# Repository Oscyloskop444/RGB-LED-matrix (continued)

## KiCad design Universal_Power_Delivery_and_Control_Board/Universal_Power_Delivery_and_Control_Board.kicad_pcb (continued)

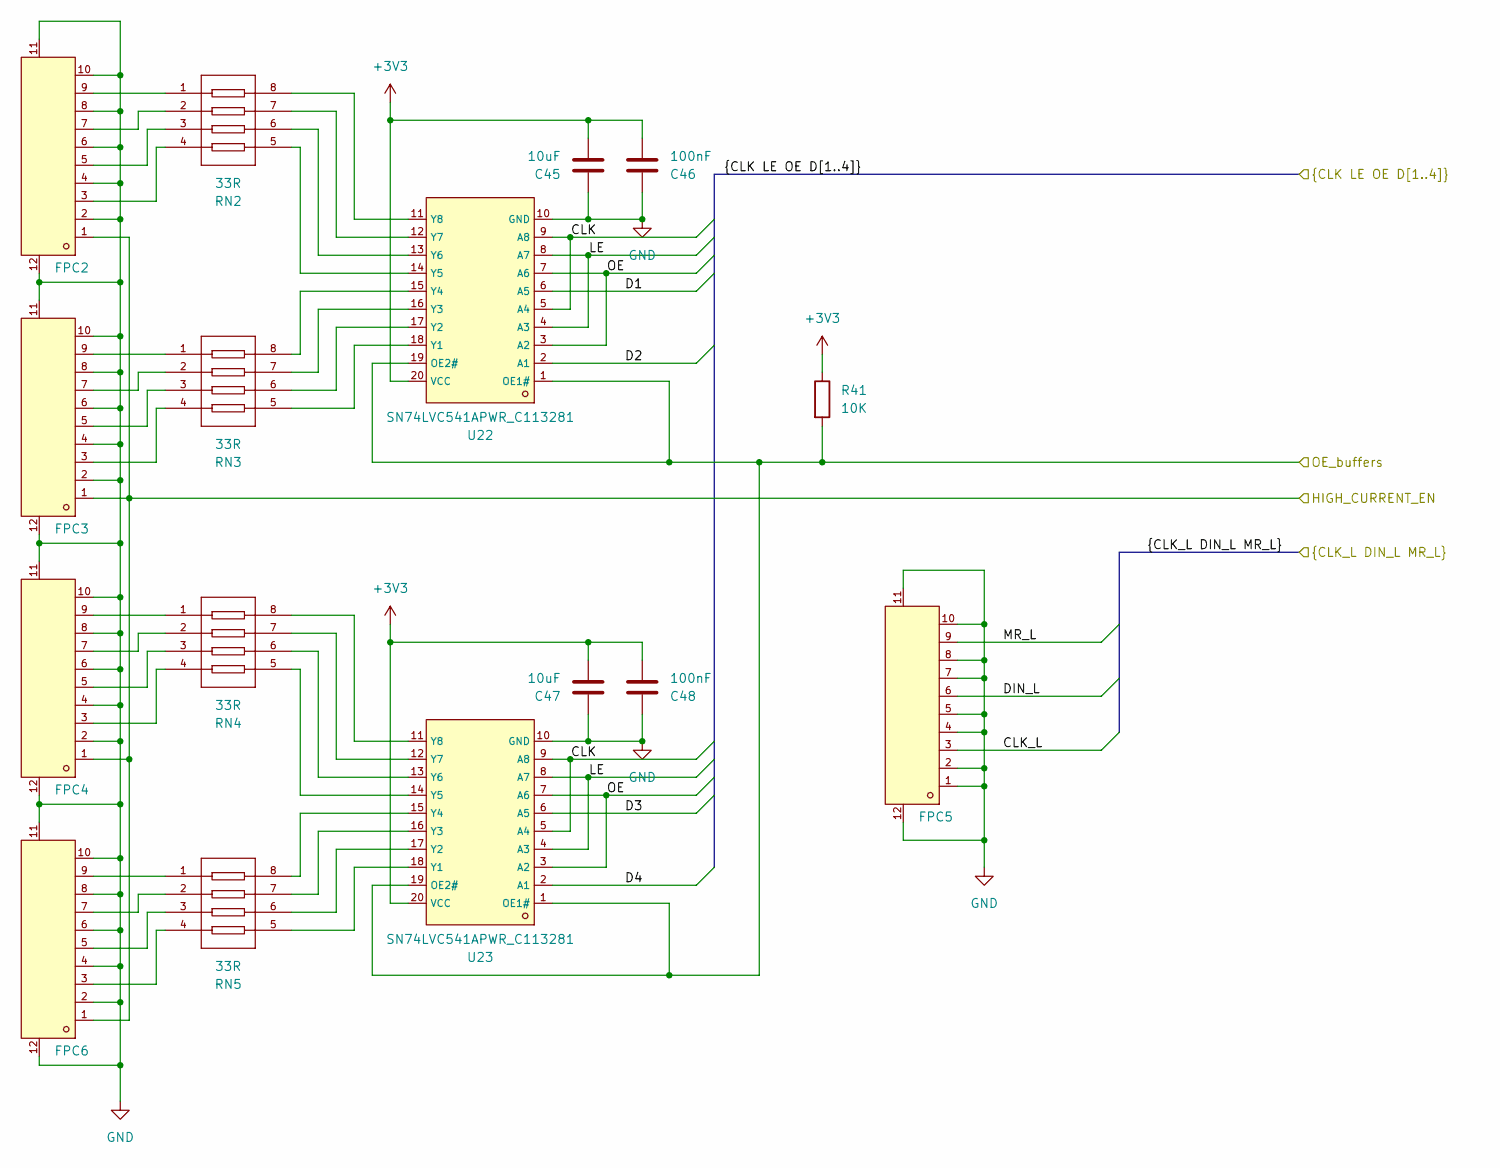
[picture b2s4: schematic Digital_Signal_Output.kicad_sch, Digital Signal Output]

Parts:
C45, C47: 10uF; C_0805_2012Metric_Pad1.18x1.45mm_HandSolder
C46, C48: 100nF; C_0402_1005Metric_Pad0.74x0.62mm_HandSolder
FPC2, FPC3, FPC4, FPC5, FPC6: XW05202-100R-00; C2906114_FPC-SMD_10P-P0_50_HCTL_XW05202-100R-00; LCSC C2906114
R41: 10K; R_0402_1005Metric_Pad0.72x0.64mm_HandSolder
RN2, RN3, RN4, RN5: 33R; C165956_RES-ARRAY-SMD_0603-8P-L3_2-W1_6-BL; LCSC C165956
U22, U23: SN74LVC541APWR_C113281; C113281_TSSOP-20_L6_5-W4_4-P0_65-LS6_4-BL; LCSC C113281

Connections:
+3V3: C45.2, C46.2, C47.2, C48.2, R41.1, U22.20 (VCC), U23.20 (VCC); also elsewhere on the board
/Digital_Signal_Output/CLK_L: FPC5.3; also elsewhere on the board
/Digital_Signal_Output/D1: U22.6 (A5); also elsewhere on the board
/Digital_Signal_Output/D2: U22.2 (A1); also elsewhere on the board
/Digital_Signal_Output/D3: U23.6 (A5); also elsewhere on the board
/Digital_Signal_Output/D4: U23.2 (A1); also elsewhere on the board
/Digital_Signal_Output/DIN_L: FPC5.6; also elsewhere on the board
/Digital_Signal_Output/HIGH_CURRENT_EN: FPC2.1, FPC3.1, FPC4.1, FPC6.1; also elsewhere on the board
/Digital_Signal_Output/MR_L: FPC5.9; also elsewhere on the board
/Digital_Signal_Output/OE_buffers: R41.2, U22.1 (OE1#), U22.19 (OE2#), U23.1 (OE1#), U23.19 (OE2#); also elsewhere on the board
/Power_Output/5V_O1: U22.5 (A4), U22.9 (A8), U23.5 (A4), U23.9 (A8); also elsewhere on the board
/Power_Output/5V_O2: U22.4 (A3), U22.8 (A7), U23.4 (A3), U23.8 (A7); also elsewhere on the board
/Power_Output/5V_O3: U22.3 (A2), U22.7 (A6), U23.3 (A2), U23.7 (A6); also elsewhere on the board
GND: C45.1, C46.1, C47.1, C48.1, FPC2.2, FPC2.4, FPC2.6, FPC2.8, FPC2.10, FPC2.11, FPC2.12, FPC3.2, FPC3.4, FPC3.6, FPC3.8, FPC3.10, FPC3.11, FPC3.12, FPC4.2, FPC4.4, FPC4.6, FPC4.8, FPC4.10, FPC4.11, FPC4.12, FPC5.1, FPC5.2, FPC5.4, FPC5.5, FPC5.7, FPC5.8, FPC5.10, FPC5.11, FPC5.12, FPC6.2, FPC6.4, FPC6.6, FPC6.8, FPC6.10, FPC6.11, FPC6.12, U22.10 (GND), U23.10 (GND); also elsewhere on the board
unnamed: FPC2.3, RN2.4
unnamed: FPC2.5, RN2.3
unnamed: FPC2.7, RN2.2
unnamed: FPC2.9, RN2.1
unnamed: FPC3.3, RN3.4
unnamed: FPC3.5, RN3.3
unnamed: FPC3.7, RN3.2
unnamed: FPC3.9, RN3.1
unnamed: FPC4.3, RN4.4
unnamed: FPC4.5, RN4.3
unnamed: FPC4.7, RN4.2
unnamed: FPC4.9, RN4.1
unnamed: FPC6.3, RN5.4
unnamed: FPC6.5, RN5.3
unnamed: FPC6.7, RN5.2
unnamed: FPC6.9, RN5.1
unnamed: RN3.5, U22.18 (Y1)
unnamed: RN3.6, U22.17 (Y2)
unnamed: RN3.7, U22.16 (Y3)
unnamed: RN3.8, U22.15 (Y4)
unnamed: RN2.5, U22.14 (Y5)
unnamed: RN2.6, U22.13 (Y6)
unnamed: RN2.7, U22.12 (Y7)
unnamed: RN2.8, U22.11 (Y8)
unnamed: RN5.5, U23.18 (Y1)
unnamed: RN5.6, U23.17 (Y2)
unnamed: RN5.7, U23.16 (Y3)
unnamed: RN5.8, U23.15 (Y4)
unnamed: RN4.5, U23.14 (Y5)
unnamed: RN4.6, U23.13 (Y6)
unnamed: RN4.7, U23.12 (Y7)
unnamed: RN4.8, U23.11 (Y8)

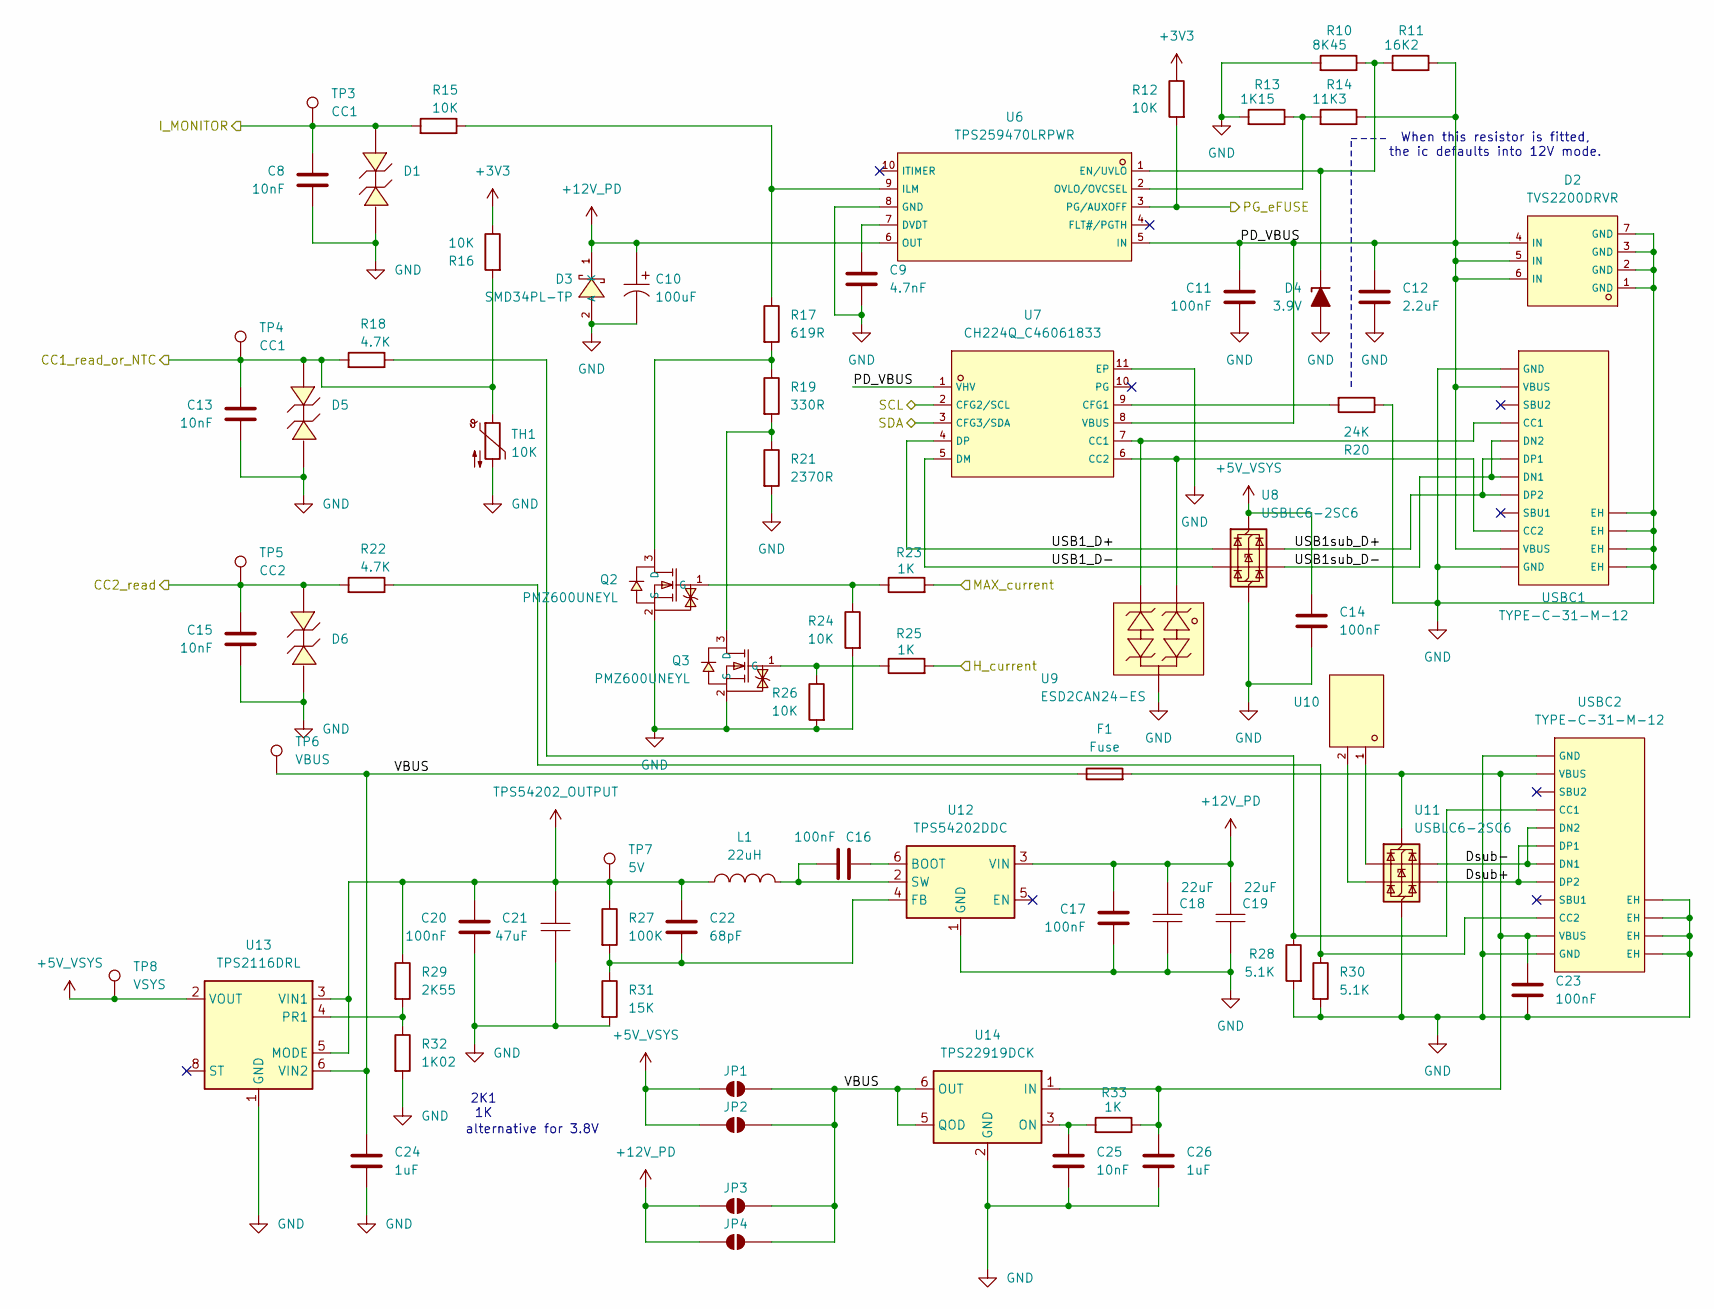
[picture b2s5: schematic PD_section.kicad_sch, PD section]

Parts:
C8, C13, C15, C25: 10nF; C_0402_1005Metric_Pad0.74x0.62mm_HandSolder
C9: 4.7nF; C_0402_1005Metric
C10: 100uF; C19673858_CAP-SMD_BD6_3-L6_5-W6_5-LS7_2-FD_1; LCSC C19673858
C11, C14, C16, C17, C20, C23: 100nF; C_0402_1005Metric_Pad0.74x0.62mm_HandSolder
C12: 2.2uF; C_0805_2012Metric
C18, C19: 22uF; C778721_C1210; LCSC C778721
C21: 47uF; C426659_C1206; LCSC C426659
C22: 68pF; C_0402_1005Metric_Pad0.74x0.62mm_HandSolder
C24: 1uF; C_0402_1005Metric_Pad0.74x0.62mm_HandSolder
C26: 1uF; C_0603_1608Metric_Pad1.08x0.95mm_HandSolder
D1, D5, D6: PESDNC2FD3V3BS; C496536_DFN1006-2L-BI; LCSC C496536
D2: TVS2200DRVR; C523793_WSON-6_L2_0-W2_0-P0_65-BL-EP; LCSC C523793
D3: SMD34PL-TP; C725481_SOD-123FL_L2_8-W1_7-LS3_6-RD; LCSC C725481
D4: 3.9V; D_SOD-882
F1: Fuse; Fuse_1206_3216Metric_Pad1.42x1.75mm_HandSolder
JP1, JP2, JP3, JP4: SolderJumper_2_Open; SolderJumper-2_P1.3mm_Open_RoundedPad1.0x1.5mm
L1: 22uH; C138686_IND-SMD_L10_7-W10_0; LCSC C138686
Q2, Q3: PMZ600UNEYL; C547286_SOT-883-3_L1_0-W0_6-BR; LCSC C547286
R10: 8K45; R_0402_1005Metric_Pad0.72x0.64mm_HandSolder
R11: 16K2; R_0402_1005Metric_Pad0.72x0.64mm_HandSolder
R12, R15, R16: 10K; R_0402_1005Metric_Pad0.72x0.64mm_HandSolder
R13: 1K15; R_0402_1005Metric_Pad0.72x0.64mm_HandSolder
R14: 11K3; R_0402_1005Metric_Pad0.72x0.64mm_HandSolder
R17: 619R; R_0402_1005Metric
R18, R22: 4.7K; R_0402_1005Metric_Pad0.72x0.64mm_HandSolder
R19: 330R; R_0402_1005Metric
R20: 24K; R_0402_1005Metric_Pad0.72x0.64mm_HandSolder
R21: 2370R; R_0402_1005Metric
R23, R25, R33: 1K; R_0402_1005Metric_Pad0.72x0.64mm_HandSolder
R24, R26: 10K; R_0402_1005Metric
R27: 100K; R_0402_1005Metric_Pad0.72x0.64mm_HandSolder
R28, R30: 5.1K; R_0402_1005Metric_Pad0.72x0.64mm_HandSolder
R29: 2K55; R_0402_1005Metric_Pad0.72x0.64mm_HandSolder
R31: 15K; R_0402_1005Metric_Pad0.72x0.64mm_HandSolder
R32: 1K02; R_0402_1005Metric_Pad0.72x0.64mm_HandSolder
TH1: 10K; R_0402_1005Metric_Pad0.72x0.64mm_HandSolder
TP3, TP4: CC1; TestPoint_Pad_D1.0mm
TP5: CC2; TestPoint_Pad_D1.0mm
TP6: VBUS; TestPoint_Pad_D1.0mm
TP7: 5V; TestPoint_Pad_D1.0mm
TP8: VSYS; TestPoint_Pad_D1.0mm
U6: TPS259470LRPWR; C3662793_VQFN-10_L2_0-W2_0-P0_45-TL; LCSC C3662793
U7: CH224Q_C46061833; C46061833_DFN-10_L2_0-W2_0-P0_40-BL-EP; LCSC C46061833
U8, U11: USBLC6-2SC6; SOT-23-6
U9: ESD2CAN24-ES; C19170841_SOT-23-3_L2_9-W1_3-P1_90-LS2_4-BR; LCSC C19170841
U10: S2B-ZR (LF)(SN); C157930_CONN-TH_S2B-ZR-LF-SN; LCSC C157930
U12: TPS54202DDC; SOT-23-6
U13: TPS2116DRL; SOT-583-8
U14: TPS22919DCK; SOT-363_SC-70-6
USBC1, USBC2: TYPE-C-31-M-12; C165948_USB-C_SMD-TYPE-C-31-M-12_1; LCSC C165948

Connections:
+3V3: R12.1, R16.1; also elsewhere on the board
+5V_VSYS: C14.1, JP1.1 (A), JP2.1 (A), TP8.1 (1_1), U8.5 (VBUS), U13.2 (VOUT), U13.7 (VOUT); also elsewhere on the board
+12V_PD: C10.1, C17.1, C18.2, C19.2, D3.1 (K), JP3.1 (A), JP4.1 (A), U6.6 (OUT), U12.3 (VIN); also elsewhere on the board
/P00: R12.2, U6.3 (PG/AUXOFF); also elsewhere on the board
/PD_Section/CC1_read_or_NTC: C13.1, D5.2, R16.2, R18.2, TH1.1, TP4.1 (1_1); also elsewhere on the board
/PD_Section/CC2_read: C15.1, D6.2, R22.2, TP5.1 (1_1); also elsewhere on the board
/PD_Section/Dsub+: U11.4 (I/O2), USBC2.A6 (DP1), USBC2.B6 (DP2)
/PD_Section/Dsub-: U11.6 (I/O1), USBC2.A7 (DN1), USBC2.B7 (DN2)
/PD_Section/H_current: R25.2; also elsewhere on the board
/PD_Section/I_MONITOR: C8.1, D1.2, R15.2, TP3.1 (1_1); also elsewhere on the board
/PD_Section/MAX_current: R23.2; also elsewhere on the board
/PD_Section/PD_VBUS: C11.1, C12.1, D2.4 (IN), D2.5 (IN), D2.6 (IN), R11.1, R14.1, U6.5 (IN), U7.1 (VHV), U7.8 (VBUS), USBC1.A4B9 (VBUS), USBC1.B4A9 (VBUS)
/PD_Section/USB1_D+: U7.4 (DP), U8.1 (I/O1)
/PD_Section/USB1_D-: U7.5 (DM), U8.3 (I/O2)
/PD_Section/USB1sub_D+: U8.6 (I/O1), USBC1.A6 (DP1), USBC1.B6 (DP2)
/PD_Section/USB1sub_D-: U8.4 (I/O2), USBC1.A7 (DN1), USBC1.B7 (DN2)
/PD_Section/VBUS: C24.1, F1.1, JP1.2 (B), JP2.2 (B), JP3.2 (B), JP4.2 (B), TP6.1 (1_1), U13.6 (VIN2), U14.5 (QOD), U14.6 (OUT)
/SCL: U7.2 (CFG2/SCL); also elsewhere on the board
/SDA: U7.3 (CFG3/SDA); also elsewhere on the board
GND: C8.2, C9.2, C10.2, C11.2, C12.2, C13.2, C14.2, C15.2, C17.2, C18.1, C19.1, C20.2, C21.1, C23.2, C24.2, C25.2, C26.2, D1.1, D2.1 (GND), D2.2 (GND), D2.3 (GND), D2.7 (GND), D3.2 (A), D4.2 (A), D5.1, D6.1, Q2.2 (S), Q3.2 (S), R10.2, R13.2, R20.1, R21.2, R24.2, R26.2, R28.2, R30.2, R31.2, R32.2, TH1.2, U6.8 (GND), U7.11 (EP), U8.2 (GND), U9.3 (GND), U11.2 (GND), U12.1 (GND), U13.1 (GND), U14.2 (GND), USBC1.1 (EH), USBC1.2 (EH), USBC1.3 (EH), USBC1.4 (EH), USBC1.A1B12 (GND), USBC1.B1A12 (GND), USBC2.1 (EH), USBC2.2 (EH), USBC2.3 (EH), USBC2.4 (EH), USBC2.A1B12 (GND), USBC2.B1A12 (GND); also elsewhere on the board
unnamed: D4.1 (K), R10.1, R11.2, U6.1 (EN/UVLO)
unnamed: Q2.3 (D), R17.2, R19.1
unnamed: Q2.1 (G), R23.1, R24.1
unnamed: Q3.3 (D), R19.2, R21.1
unnamed: Q3.1 (G), R25.1, R26.1
unnamed: C9.1, U6.7 (DVDT)
unnamed: R15.1, R17.1, U6.9 (ILM)
unnamed: R13.1, R14.2, U6.2 (OVLO/OVCSEL)
unnamed: U7.7 (CC1), U9.2 (IO), USBC1.A5 (CC1)
unnamed: U7.6 (CC2), U9.1 (IO), USBC1.B5 (CC2)
unnamed: R20.2, U7.9 (CFG1)
unnamed: U10.1, U11.1 (I/O1)
unnamed: U10.2, U11.3 (I/O2)
unnamed: C23.1, C26.1, F1.2, R33.1, U11.5 (VBUS), U14.1 (IN), USBC2.A4B9 (VBUS), USBC2.B4A9 (VBUS)
unnamed: C16.1, U12.6 (BOOT)
unnamed: C22.2, R27.2, R31.1, U12.4 (FB)
unnamed: C16.2, L1.1, U12.2 (SW)
unnamed: R29.2, R32.1, U13.4 (PR1)
unnamed: C25.1, R33.2, U14.3 (ON)
unnamed: R18.1, R28.1, USBC2.A5 (CC1)
unnamed: R22.1, R30.1, USBC2.B5 (CC2)
TPS54202_OUTPUT: C20.1, C21.2, C22.1, L1.2, R27.1, R29.1, TP7.1 (1_1), U13.3 (VIN1), U13.5 (MODE); also elsewhere on the board

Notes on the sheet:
2K1 1K
alternative for 3.8V
When this resistor is fitted, the ic defaults into 12V mode.

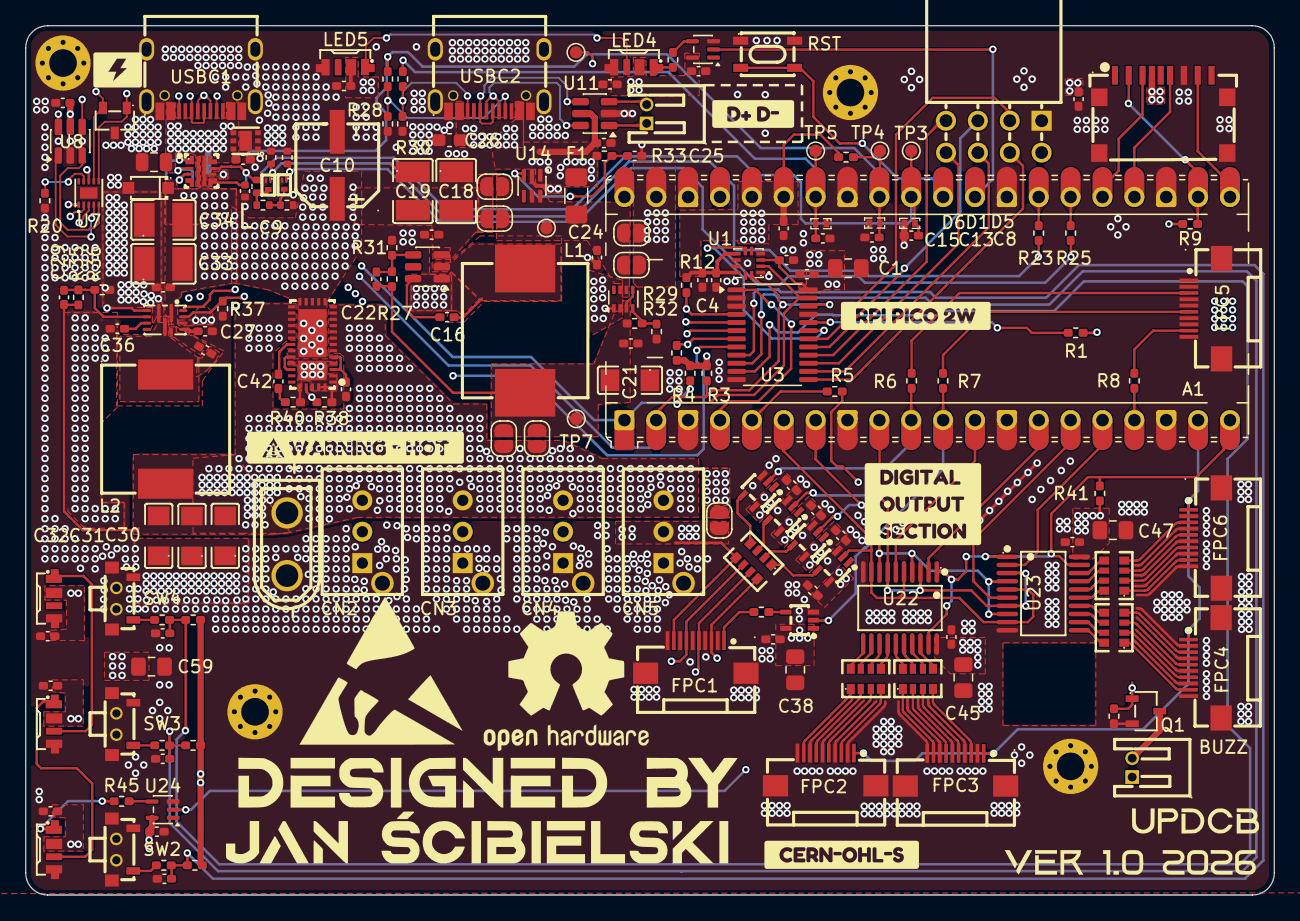
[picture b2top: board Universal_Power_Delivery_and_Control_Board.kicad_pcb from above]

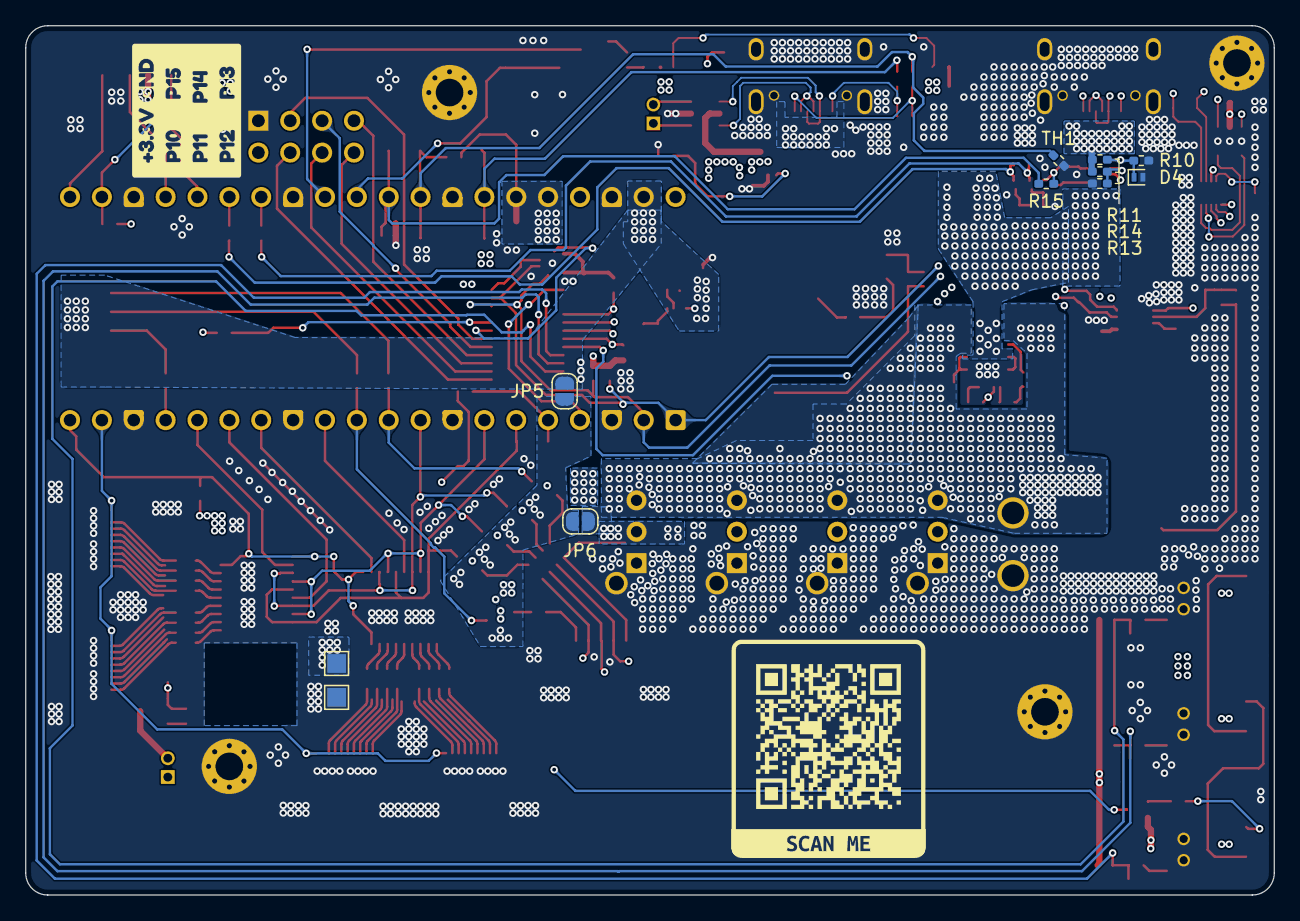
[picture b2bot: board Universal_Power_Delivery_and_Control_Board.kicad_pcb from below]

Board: 4 copper layers, 99.5 x 69.3 mm, 203 parts (13 on the bottom side), 144 nets.

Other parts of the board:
kobee-studio-6AA926CC: Kobee Studio; kobee-studio-6AA92563
kobee-studio-6AA928EB: Kobee Studio; kobee-studio-6AA928EB
kobee-studio-6AA996C7: Kobee Studio; kobee-studio-6AA996C7
kobee-studio-6AA9969D: Kobee Studio; kobee-studio-6AA9969D
kobee-studio-6AA92292: Kobee Studio; kobee-studio-6AA92292
kobee-studio-6AA92370: Kobee Studio; kobee-studio-6AA92370
kobee-studio-6AA92863: Kobee Studio; kobee-studio-6AA92822
kobee-studio-6AA99759: Kobee Studio; kobee-studio-6AA99759

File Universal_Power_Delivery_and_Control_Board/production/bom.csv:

Designator,Footprint,Quantity,Value,LCSC Part #
A1,RaspberryPi_Pico_Common_Unspecified,1,RaspberryPi_Pico,
"C1, C38, C45, C47, C59",0805,5,10uF,
C10,C19673858_CAP-SMD_BD6_3-L6_5-W6_5-LS7_2-FD_1,1,100uF,C19673858
"C11, C14, C16, C17, C2, C20, C23, C28, C3, C35, C36, C37, C39, C40, C41, C43, C44, C46, C48, C49, C5, C50, C51, C52, C53, C54, C55, C56, C57, C58, C6, C7",0402,32,100nF,
C12,0805,1,2.2uF,
"C13, C15, C25, C8",0402,4,10nF,
"C18, C19, C33, C34",C778721_C1210,4,22uF,C778721
"C21, C30, C31, C32",C426659_C1206,4,47uF,C426659
C22,0402,1,68pF,
"C24, C27, C4",0402,3,1uF,
C26,0603,1,1uF,
C29,0402,1,22pF,
C42,0402,1,160nF,
C9,0402,1,4.7nF,
CN1,C428721_CONN-TH_XT30UPB-M,1,XT30UPB-M,C428721
"CN2, CN3, CN4, CN5",C264992_CONN-TH_B03B-XASK-1-A-LF-SN,4,B03B-XASK-1-A(LF)(SN),C264992
"D1, D5, D6",C496536_DFN1006-2L-BI,3,PESDNC2FD3V3BS,C496536
D2,C523793_WSON-6_L2_0-W2_0-P0_65-BL-EP,1,TVS2200DRVR,C523793
D3,C725481_SOD-123FL_L2_8-W1_7-LS3_6-RD,1,SMD34PL-TP,C725481
D4,D_SOD-882,1,3.9V,
F1,1206,1,Fuse,
"FPC1, FPC2, FPC3, FPC4, FPC5, FPC6",C2906114_FPC-SMD_10P-P0_50_HCTL_XW05202-100R-00,6,XW05202-100R-00,C2906114
L1,C138686_IND-SMD_L10_7-W10_0,1,22uH,C138686
L2,C845068_IND-SMD_L10_2-W10_2-LS10_8,1,1uH,C845068
"LED1, LED2, LED3, LED4, LED5",C5378721_LED-SMD_4P-L4_0-W1_6-L,5,SK6812SIDE-A_C5378721,C5378721
Q1,C42443455_SOT-23-3_L2_9-W1_5-P2_0-LS2_5-BR,1,JTD2302,C42443455
"Q2, Q3",C547286_SOT-883-3_L1_0-W0_6-BR,2,PMZ600UNEYL,C547286
"R1, R23, R25, R33, R40",0402,5,1K,
R10,0402,1,8K45,
R11,0402,1,16K2,
"R12, R15, R16, R2, R24, R26, R34, R38, R41, R46, R47, R48, R9, TH1",0402,14,10K,
R13,0402,1,1K15,
R14,0402,1,11K3,
R17,0402,1,619R,
"R18, R22, R3, R4",0402,4,4.7K,
R19,0402,1,330R,
R20,0402,1,24K,
R21,0402,1,2370R,
"R27, R37, R42, R43, R44",0402,5,100K,
"R28, R30",0402,2,5.1K,
R29,0402,1,2K55,
R31,0402,1,15K,
R32,0402,1,1K02,
R35,0402,1,120K,
R36,0402,1,20K,
"R39, R5, R6, R7, R8",0402,5,33R,
"R45, R49",0402,2,470R,
RN1,C165956_RES-ARRAY-SMD_0603-8P-L3_2-W1_6-BL,1,YC164-JR-0733RL,C165956
"RN2, RN3, RN4, RN5",C165956_RES-ARRAY-SMD_0603-8P-L3_2-W1_6-BL,4,33R,C165956
SW1,C2888428_SW-SMD_4P-L4_2-W3_3-P2_15-LS4_6,1,TSA016A2526A,C2888428
"SW2, SW3, SW4",C36936640_SW-SMD_TS1102-TD35HBM,3,TS1102-TD35HBM,C36936640
"TP1, TP2",TestPoint_Pad_1.5x1.5mm,2,TestPoint,
"TP3, TP4",TestPoint_Pad_D1.0mm,2,CC1,
TP5,TestPoint_Pad_D1.0mm,1,CC2,
TP6,TestPoint_Pad_D1.0mm,1,VBUS,
TP7,TestPoint_Pad_D1.0mm,1,5V,
TP8,TestPoint_Pad_D1.0mm,1,VSYS,
U1,C19274408_LGA-12_L2_0-W2_0-P0_50-TL,1,SC7A20HTR,C19274408
"U10, U2",C157930_CONN-TH_S2B-ZR-LF-SN,2,S2B-ZR (LF)(SN),C157930
"U11, U8",SOT-23-6,2,USBLC6-2SC6,
U12,SOT-23-6,1,TPS54202DDC,
U13,SOT-583-8,1,TPS2116DRL,
U14,SOT-363_SC-70-6,1,TPS22919DCK,
U15,C22418767_QFN-12_L3_0-W2_0-P0_5-TL_NB680,1,TPS51385RJNR,C22418767
"U16, U17, U18, U20, U21",C10425_SC-70-5_L2_1-W1_3-P0_65-LS2_1-BR,5,SN74LVC1G17DCKR,C10425
U19,C2653596_VQFN-36_L7_0-W3_5-P0_50-BL-EP,1,TPS24751RUVR,C2653596
"U22, U23",C113281_TSSOP-20_L6_5-W4_4-P0_65-LS6_4-BL,2,SN74LVC541APWR_C113281,C113281
"U24, U25",SOT-353_SC-70-5,2,SN74LV1T34DCK,
U3,TSSOP-24_4.4x7.8mm_P0.65mm,1,TCA9555PWR,
U4,C42163146_HDR-TH_8P-P2_54-H-F-R2-C4-S2_54-W8_5,1,HC-PM254-8.5H-2X4PW-02A,C42163146
U5,C5362199_TF-SMD_XKTF-0803-0,1,TF-0803-0,C5362199
U6,C3662793_VQFN-10_L2_0-W2_0-P0_45-TL,1,TPS259470LRPWR,C3662793
U7,C46061833_DFN-10_L2_0-W2_0-P0_40-BL-EP,1,CH224Q_C46061833,C46061833
U9,C19170841_SOT-23-3_L2_9-W1_3-P1_90-LS2_4-BR,1,ESD2CAN24-ES,C19170841
"USBC1, USBC2",C165948_USB-C_SMD-TYPE-C-31-M-12_1,2,TYPE-C-31-M-12,C165948

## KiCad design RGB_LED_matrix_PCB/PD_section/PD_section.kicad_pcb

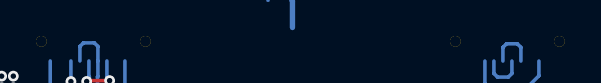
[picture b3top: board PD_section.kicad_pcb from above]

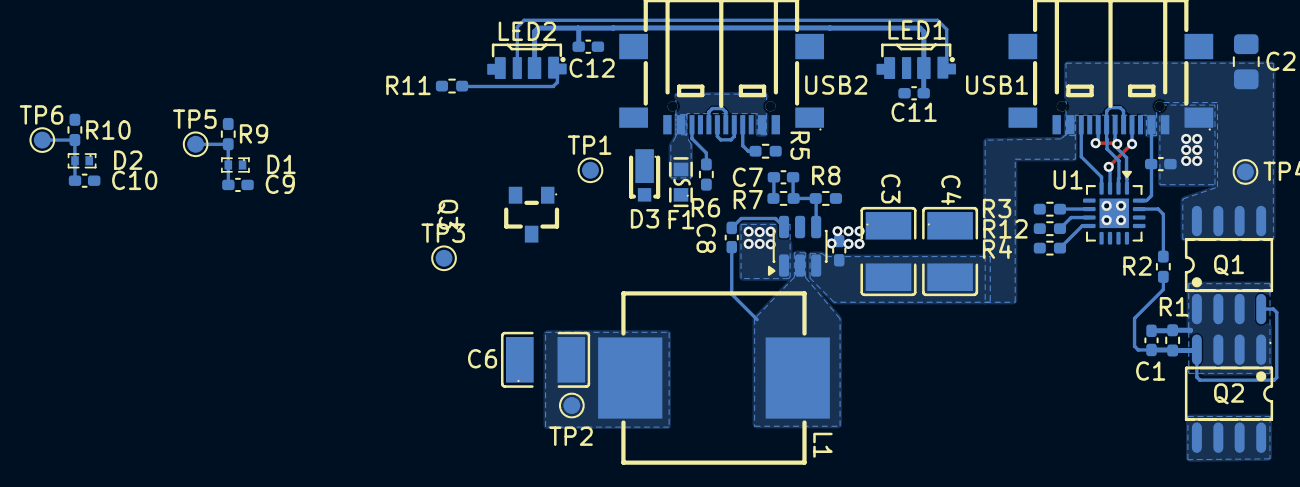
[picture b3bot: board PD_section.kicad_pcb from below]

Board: 2 copper layers, 45 parts (45 on the bottom side), 29 nets.

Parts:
C1: 1nF; C_0402_1005Metric_Pad0.74x0.62mm_HandSolder
C2: 1uF; C_0805_2012Metric_Pad1.18x1.45mm_HandSolder
C3, C4: 22uF; C778721_C1210
C5, C8, C11, C12, C13: 100nF; C_0402_1005Metric_Pad0.74x0.62mm_HandSolder
C6: 47uF; C77101_C1210
C7: 68pF; C_0402_1005Metric_Pad0.74x0.62mm_HandSolder
C9, C10: 10nF; C_0402_1005Metric_Pad0.74x0.62mm_HandSolder
D1, D2: PESDNC2FD3V3BS; C496536_DFN1006-2L-BI
D3: MSP5.0A-M3/89A; C2649890_DO-219AD_L2_2-W1_3-FD
F1: 06H1100D; C182303_F0603
L1: 22uH; C138686_IND-SMD_L10_7-W10_0
LED1, LED2: SK6812SIDE-A_C5378721; C5378721_LED-SMD_4P-L4_0-W1_6-L
Q1, Q2: AO4407A; C16072_SOIC-8_L4_9-W3_9-P1_27-LS6_0-BL
Q3: AO3401A; C15127_SOT-23_L2_9-W1_3-P1_90-LS2_4-BR
R1: 10K; R_0402_1005Metric_Pad0.72x0.64mm_HandSolder
R2, R9, R10: 1K; R_0402_1005Metric_Pad0.72x0.64mm_HandSolder
R3, R4, R12: 900K; R_0402_1005Metric_Pad0.72x0.64mm_HandSolder
R5, R6: 5.1K; R_0402_1005Metric_Pad0.72x0.64mm_HandSolder
R7: 100K; R_0402_1005Metric_Pad0.72x0.64mm_HandSolder
R8: 13.3K; R_0402_1005Metric_Pad0.72x0.64mm_HandSolder
R11: 470R; R_0402_1005Metric_Pad0.72x0.64mm_HandSolder
TP1: VBUS; TestPoint_Pad_D1.0mm
TP2: 5V; TestPoint_Pad_D1.0mm
TP3: VSYS; TestPoint_Pad_D1.0mm
TP4: PD; TestPoint_Pad_D1.0mm
TP5: CC1; TestPoint_Pad_D1.0mm
TP6: CC2; TestPoint_Pad_D1.0mm
U1: HUSB238A-xxxxx-QN16R; WQFN-16-1EP_3x3mm_P0.5mm_EP1.75x1.75mm
U2: TPS54202DDC; SOT-23-6
USB1, USB2: TYPE-C 16P QTGM027; C5187472_USB-TYPE-C-SMD_TYPE-C-16P-QTWT

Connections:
+3V3: R12.1, U1.5 (VDD)
+5V_VBUS: D3.2 (C), F1.1, Q3.1 (G), TP1.1 (1_1)
+5V_VSYS: C11.1, C12.1, LED1.2 (VDD), LED2.2 (VDD), Q3.3 (D), TP3.1 (1_1)
+12V_PD: Q2.5 (D), Q2.6 (D), Q2.7 (D), Q2.8 (D)
/CC1_read: C9.1, D1.2, R9.2, TP5.1 (1_1)
/CC2_read: C10.1, D2.2, R10.2, TP6.1 (1_1)
/D+: USB2.A6 (DP1), USB2.B6 (DP2)
/D-: USB2.A7 (DN1), USB2.B7 (DN2)
/USB1_D+: U1.1 (D+), USB1.A6 (DP1), USB1.B6 (DP2)
/USB1_D-: U1.2 (D-), USB1.A7 (DN1), USB1.B7 (DN2)
GND: C2.2, C3.1, C4.1, C5.2, C6.1, C9.2, C10.2, C11.2, C12.2, C13.2, D1.1, D2.1, D3.1 (A), LED1.4 (GND), LED2.4 (GND), R3.2, R4.2, R5.2, R6.2, R8.2, U1.17 (GND), U2.1 (GND), USB1.0 (EH), USB1.A1B12 (GND), USB1.B1A12 (GND), USB2.0 (EH), USB2.A1B12 (GND), USB2.B1A12 (GND)
unnamed: C1.1, Q1.1 (S), Q1.2 (S), Q1.3 (S), Q2.1 (S), Q2.2 (S), Q2.3 (S), R1.1
unnamed: F1.2, USB2.A4B9 (VBUS), USB2.B4A9 (VBUS)
unnamed: LED1.1 (DIN), LED2.3 (DOUT)
unnamed: LED2.1 (DIN), R11.2
unnamed: C1.2, Q1.4 (G), Q2.4 (G), R1.2, R2.1
unnamed: C6.2, C7.1, L1.2, Q3.2 (S), R7.1, TP2.1 (1_1)
unnamed: R4.1, U1.8 (ADDR/ORIENT)
unnamed: U1.3 (CC1), USB1.A5 (CC1)
unnamed: U1.4 (CC2), USB1.B5 (CC2)
unnamed: R12.2, U1.7 (EN_HVDCP/OUT1)
unnamed: R2.2, U1.15 (GATE)
unnamed: C2.1, C3.2, C4.2, C5.1, C13.1, Q1.5 (D), Q1.6 (D), Q1.7 (D), Q1.8 (D), TP4.1 (1_1), U1.16 (VBUS), U2.3 (VIN), USB1.A4B9 (VBUS), USB1.B4A9 (VBUS)
unnamed: R3.1, U1.6 (~DEBUG)
unnamed: C8.1, U2.6 (BOOT)
unnamed: C7.2, R7.2, R8.1, U2.4 (FB)
unnamed: C8.2, L1.1, U2.2 (SW)
unnamed: R5.1, R9.1, USB2.A5 (CC1)
unnamed: R6.1, R10.1, USB2.B5 (CC2)
